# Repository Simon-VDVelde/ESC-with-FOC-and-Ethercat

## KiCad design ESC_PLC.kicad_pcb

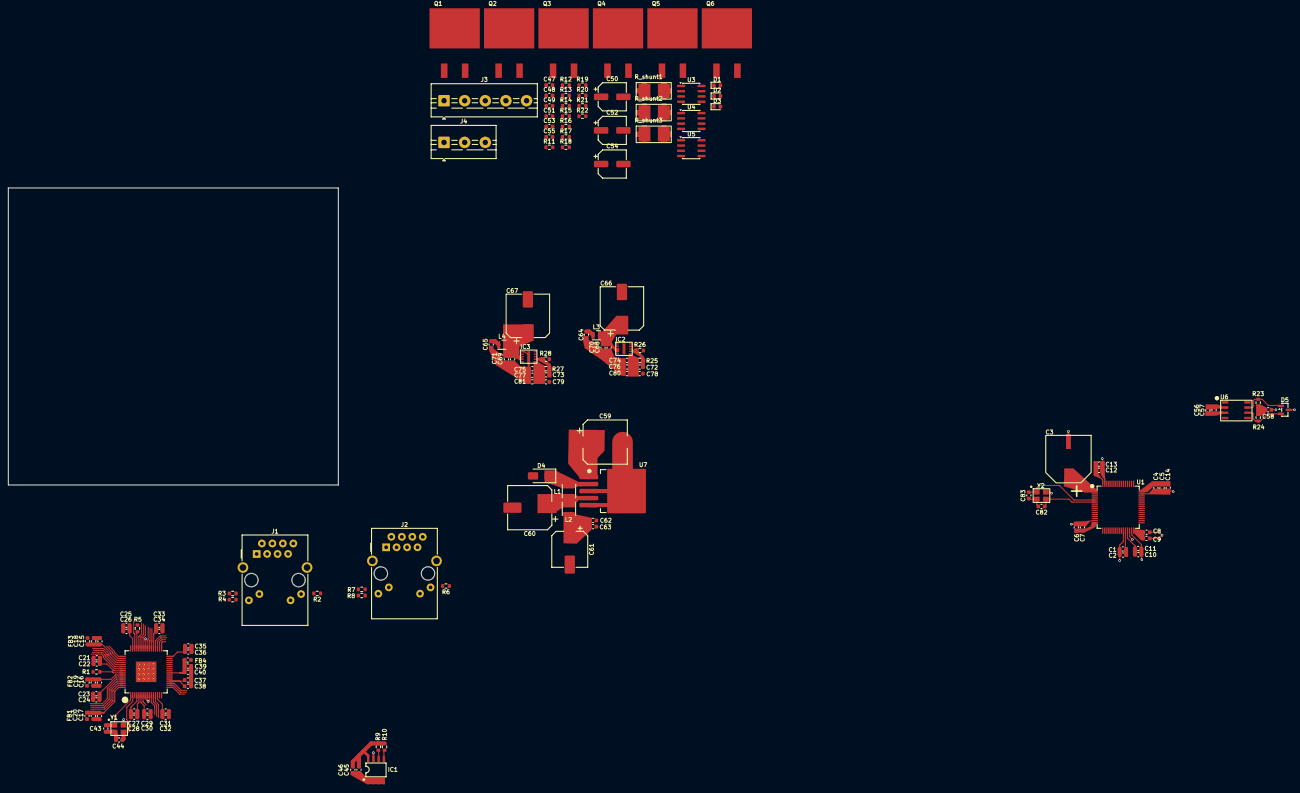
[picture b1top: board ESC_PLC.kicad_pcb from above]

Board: 2 copper layers, 80.0 x 72.0 mm, 147 parts (0 on the bottom side), 88 nets.

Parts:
C1, C5, C7, C9, C11, C13, C18, C19, C20, C22, C24, C25, C27, C30, C32, C33, C36, C38, C40, C46, C57, C63, C80, C81: 1µ; C_0603_1608Metric
C2, C4, C6, C8, C10, C12, C15, C16, C17, C21, C23, C26, C28, C31, C34, C35, C37, C39, C45, C56, C62, C78, C79: 100n; C_0603_1608Metric
C3: SuperCap 0.1F 10.5mmx10.8mm
C14, C64, C65, C68, C69, C70, C71, C74, C75, C76, C77: 10µ; C_0603_1608Metric
C29: 470p; C_0603_1608Metric
C43, C44, C82, C83: 8p; C_0603_1608Metric
C47, C48, C49, C58: 10n; C_0603_1608Metric
C50, C52, C54: 22µ; CP_Elec_6.3x5.8
C51, C53, C55: 2.2µ; C_0603_1608Metric
C59: 100µ; CP_Elec_10x10.5
C60: 330µ; CP_Elec_10x10.5
C61: 100µ; CP_Elec_8x10.5
C66, C67: 45µ; CP_Elec_10x10
C72, C73: 100p; C_0603_1608Metric
D1, D2, D3: Schottky; D_0603_1608Metric
D4: SS210; D_SMA
D5: NUP2105L; SOT-23
FB1, FB2, FB3, FB4: FerriteBead; Ferrite Bead 0603
IC1: 24AA32AF; EEPROM 32Kbit
IC2, IC3: MagI3C Power Module 171013201
J1, J2: RJ45_Amphenol_RJMG1BD3B8K1ANR
J3: Screw_Terminal_01x05; TerminalBlock_MaiXu_MX126-5.0-05P_1x05_P5.00mm
J4: Screw_Terminal_01x03; TerminalBlock_MaiXu_MX126-5.0-03P_1x03_P5.00mm
L1: 330µ; L_APV_ANR3010
L2: 20µ; L_APV_ANR3010
L3, L4: 1µ; L_Wurth_WE-LQSH-2010
Q1, Q2, Q3, Q4, Q5, Q6: STB100N10F7; STB100N10F7 Mosfet
R1: 12.1k; R_0603_1608Metric
R2, R4, R6, R8: 330; R_0603_1608Metric
R3, R5, R7, R9, R10, R14, R15, R16: 10k; R_0603_1608Metric
R11, R12, R17, R18, R20, R21: 22; R_0603_1608Metric
R13, R19, R22: 1k; R_0603_1608Metric
R23, R24: 60; R_0603_1608Metric
R25, R27: 100k; R_0603_1608Metric
R26: 32.4k; R_0603_1608Metric
R28: 19.1k; R_0603_1608Metric
R_shunt1, R_shunt2, R_shunt3: 2m; Shunt Resistor 2512
U1: stm32G474; STM32G474
U2: LAN9252
U3, U4, U5: MIC4604YM; SOIC-8_3.9x4.9mm_P1.27mm
U6: TCAN334GD
U7: TL2575HV-12; TL2575HV-12 (TO-263)
Y1: 25Mhz; 25Mhz crystal 8pF
Y2: 8Mhz; 25Mhz crystal 8pF

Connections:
+3V3: C4.1, C5.1, C6.1, C7.1, C8.1, C9.1, C10.1, C11.1, C12.1, C13.1, C14.1, C25.2, C26.2, C27.1, C28.1, C31.1, C32.1, C33.1, C34.1, C35.1, C36.1, C37.1, C38.1, C45.1, C46.1, C56.1, C57.1, C72.1, C74.1, C76.1, C78.1, C80.1, FB1.1, FB2.1, FB3.1, IC1.8 (Vcc), IC2.6 (Vout), R2.1, R5.1, R6.1, R9.1, R10.1, R14.2, R15.2, R16.2, R25.1, U1.16 (VDD), U1.29 (VDDA), U1.32 (VDD), U1.48 (VDD), U1.64 (VDD), U2.5 (VDD33), U2.7 (REG_EN), U2.14 (VDDIO), U2.20 (VDDIO), U2.32 (VDDIO), U2.37 (VDDIO), U2.47 (VDDIO), U6.3 (Vcc)
+5V: C73.1, C75.1, C77.1, C79.1, C81.1, IC3.6 (Vout), J3.5, R27.1
+12V: C50.1, C52.1, C54.1, C61.1, C62.1, C63.1, C64.1, C65.1, D1.1 (K), D2.1 (K), D3.1 (K), L2.2, L3.1, L4.1, U3.1 (VDD), U4.1 (VDD), U5.1 (VDD)
+48V: C59.1, Q1.2, Q3.2, Q5.2, U7.1 (Vin)
/BLDC/Hall_U: C47.1, J3.2, R16.1, U1.59 (PB6)
/BLDC/Hall_V: C48.1, J3.3, R15.1, U1.60 (PB7)
/BLDC/Hall_W: C49.1, J3.4, R14.1, U1.61 (PB8)
/BLDC/Motor_U_HI: U1.8 (PC0), U3.5 (HI)
/BLDC/Motor_U_LI: U1.35 (PB13), U3.6 (LI)
/BLDC/Motor_V_HI: U1.9 (PC1), U4.5 (HI)
/BLDC/Motor_V_LI: U1.36 (PB14), U4.6 (LI)
/BLDC/Motor_W_HI: U1.10 (PC2), U5.5 (HI)
/BLDC/Motor_W_LI: U1.37 (PB15), U5.6 (LI)
/BLDC/Shunt_U: R13.2, U1.13 (PA1)
/BLDC/Shunt_V: R19.2, U1.33 (PB11)
/BLDC/Shunt_W: R22.2, U1.34 (PB12)
/BLDC/U_Gate_High: R11.2, U3.3 (HO)
/BLDC/U_Gate_Low: R12.2, U3.8 (LO)
/BLDC/U_Motor: C51.2, J4.1, Q1.3, Q2.2, U3.4 (HS)
/BLDC/V_Gate_High: R17.2, U4.3 (HO)
/BLDC/V_Gate_Low: R18.2, U4.8 (LO)
/BLDC/V_Motor: C53.2, J4.2, Q3.3, Q4.2, U4.4 (HS)
/BLDC/W_Gate_High: R20.2, U5.3 (HO)
/BLDC/W_Gate_Low: R21.2, U5.8 (LO)
/BLDC/W_Motor: C55.2, J4.3, Q5.3, Q6.2, U5.4 (HS)
/CAN/CANH: D5.1 (K), R23.1, U6.7 (CANH)
/CAN/CANL: D5.2 (K), R24.2, U6.6 (CANL)
/CAN/CAN_RXD: U1.46 (PA12), U6.4 (RXD)
/CAN/CAN_TXD: U1.45 (PA11), U6.1 (TXD)
/CAN/SHDN: U1.50 (PA14), U6.5 (SHDN)
/CAN/STB: U1.49 (PA13), U6.8 (STB)
/Ethercat Sheet/EEPROM SCL: IC1.5 (SCL), R10.2, U2.43 (EESCL/TCK)
/Ethercat Sheet/EEPROM SDA: IC1.6 (SDA), R9.2, U2.42 (EESDA/TMS)
/Ethercat Sheet/LinkLed0: R4.2, U2.48 (TDO)
/Ethercat Sheet/LinkLed1: R8.1, U2.46 (TDI)
/Ethercat Sheet/OSCI: C43.1, U2.1 (OSCI), Y1.1
/Ethercat Sheet/OSCO: C44.1, U2.2 (OSCO), Y1.3
/Ethercat Sheet/QSPI_CS: U1.14 (PA2), U2.50 (D5/AD5)
/Ethercat Sheet/QSPI_SCK: U1.17 (PA3), U2.19 (D9/AD9)
/Ethercat Sheet/QSPI_SIO0: U1.25 (PB1), U2.17 (D0/AD0)
/Ethercat Sheet/QSPI_SIO1: U1.24 (PB0), U2.13 (D1/AD1)
/Ethercat Sheet/QSPI_SIO2: U1.21 (PA7), U2.12 (D2/AD2)
/Ethercat Sheet/QSPI_SIO3: U1.20 (PA6), U2.35 (D3/AD3/WD_TRIG/SIO3)
/Ethercat Sheet/RBias: R1.1, U2.57 (RBIAS)
/Ethercat Sheet/RXNA: J1.R6 (RD-), U2.54 (RXNA)
/Ethercat Sheet/RXNB: J2.R6 (RD-), U2.61 (RXNB)
/Ethercat Sheet/RXPA: J1.R3 (RD+), U2.55 (RXPA)
/Ethercat Sheet/RXPB: J2.R3 (RD+), U2.60 (RXPB)
/Ethercat Sheet/RunLed: J1.L2, J2.L2, R5.2, U2.45 (RUNLED)
/Ethercat Sheet/TXNA: J1.R2 (TD-), U2.52 (TXNA)
/Ethercat Sheet/TXNB: J2.R2 (TD-), U2.63 (TXNB)
/Ethercat Sheet/TXPA: J1.R1 (TD+), U2.53 (TXPA)
/Ethercat Sheet/TXPB: J2.R1 (TD+), U2.62 (TXPB)
/Ethercat Sheet/TXRX1: C15.1, C18.1, FB3.2, J1.R4 (TCT), J1.R5 (RCT), U2.51 (VDD33TXRX1)
/Ethercat Sheet/TXRX2: C17.1, C20.1, FB1.2, J2.R4 (TCT), J2.R5 (RCT), U2.64 (VDD33TXRX2)
/Ethercat Sheet/VDD33Bias: C16.1, C19.1, FB2.2, U2.58 (VDD33BIAS)
/Ethercat Sheet/VDD1212TX: C21.1, C22.1, C23.1, C24.1, FB4.1, U2.56 (VDD12TX1), U2.59 (VDD1212TX2)
/Ethercat Sheet/VDDCR: C29.1, C30.1, C39.1, C40.1, FB4.2, U2.6 (VDDCR), U2.24 (VDDCR), U2.38 (VDDCR)
/Power Sheet/12To3.3Vin: C66.1, C68.1, C70.1, IC2.3 (Vin), IC2.4 (EN), L3.2
/Power Sheet/12To5Vin: C67.1, C69.1, C71.1, IC3.3 (Vin), IC3.4 (EN), L4.2
/µcontroller/OSC_IN: C83.1, U1.5 (PF0), Y2.1
/µcontroller/OSC_OUT: C82.1, U1.6 (PF1), Y2.3
GND: C1.2, C2.2, C3.2, C4.2, C5.2, C6.2, C7.2, C8.2, C9.2, C10.2, C11.2, C12.2, C13.2, C14.2, C15.2, C16.2, C17.2, C18.2, C19.2, C20.2, C21.2, C22.2, C23.2, C24.2, C25.1, C26.1, C27.2, C28.2, C29.2, C30.2, C31.2, C32.2, C33.2, C34.2, C35.2, C36.2, C37.2, C38.2, C39.2, C40.2, C43.2, C44.2, C45.2, C46.2, C47.2, C48.2, C49.2, C50.2, C52.2, C54.2, C56.2, C57.2, C58.2, C59.2, C60.2, C61.2, C62.2, C63.2, C64.2, C65.2, C66.2, C67.2, C68.2, C69.2, C70.2, C71.2, C74.2, C75.2, C76.2, C77.2, C78.2, C79.2, C80.2, C81.2, C82.2, C83.2, D4.2 (A), D5.3 (A), IC1.1 (A0), IC1.2 (A1), IC1.3 (A2), IC1.4 (Vss), IC1.7 (WP), IC2.1 (GND), IC2.11 (GND), IC3.1 (GND), IC3.11 (GND), J1.SH, J2.SH, J3.1, R1.2, R3.2, R7.2, R26.2, R28.2, R_shunt1.2, R_shunt2.2, R_shunt3.2, U1.15 (VSS), U1.27 (VSSA), U1.31 (VSS), U1.47 (VSS), U1.63 (VSS), U2.4 (oscvss), U2.8 (EXLOSEN), U2.9 (FXSDA/FXLOSA/FXSDENA), U2.10 (FXSDB/FXLOSB/FXSDENB), U2.41 (TESTMODE), U3.7 (VSS), U4.7 (VSS), U5.7 (VSS), U6.2 (GND), U7.3 (GND), U7.5 (EN), Y1.2 (GND), Y1.4 (GND), Y2.2 (GND), Y2.4 (GND)
unnamed: C58.1, R23.2, R24.1
unnamed: C51.1, D1.2 (A), U3.2 (HB)
unnamed: C53.1, D2.2 (A), U4.2 (HB)
unnamed: C55.1, D3.2 (A), U5.2 (HB)
unnamed: D4.1 (K), L1.1, U7.2 (Vout)
unnamed: C72.2, IC2.7 (FB), R25.2, R26.1
unnamed: C73.2, IC3.7 (FB), R27.2, R28.1
unnamed: J1.L1, R2.2
unnamed: J1.L3, R3.1
unnamed: J1.L4, R4.1
unnamed: J2.L1, R6.2
unnamed: J2.L3, R7.1
unnamed: J2.L4, R8.2
unnamed: Q1.1, R11.1
unnamed: Q2.1, R12.1
unnamed: Q2.3, R13.1, R_shunt1.1
unnamed: Q3.1, R17.1
unnamed: Q4.1, R18.1
unnamed: Q4.3, R19.1, R_shunt2.1
unnamed: Q5.1, R20.1
unnamed: Q6.1, R21.1
unnamed: Q6.3, R22.1, R_shunt3.1
unnamed: C3.1, U1.1 (VBAT)
unnamed: C1.1, C2.1, U1.28 (VREF+)
unnamed: C60.1, L1.2, L2.1, U7.4 (FB)
